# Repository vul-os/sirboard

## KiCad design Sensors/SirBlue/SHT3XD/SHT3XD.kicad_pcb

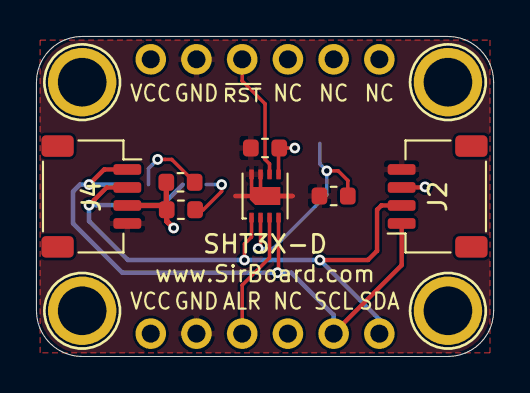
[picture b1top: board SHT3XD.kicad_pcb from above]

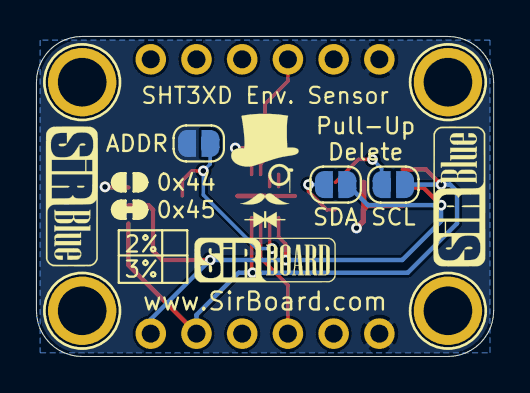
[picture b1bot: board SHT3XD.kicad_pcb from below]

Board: 2 copper layers, 25.4 x 17.8 mm, 16 parts (5 on the bottom side), 9 nets.

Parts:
ADDR: SolderJumper_2_Open; SolderJumper-2_P1.3mm_Open_RoundedPad1.0x1.5mm
C1: C; C_0603_1608Metric
H1, H2, H3, H4: MountingHole; MountingHole_M2.5_SirBoard
J1, J3: Conn_01x06; PinHeader_1x06_P2.54mm_Vertical
J2, J4: Conn_01x04; JST_SH_SM04B-SRSS-TB_1x04-1MP_P1.00mm_Horizontal
R1, R2, R3: 10K; R_0603_1608Metric
SCL: SolderJumper_2_Open; SolderJumper-2_P1.3mm_Open_RoundedPad1.0x1.5mm
SDA: SolderJumper_2_Open; SolderJumper-2_P1.3mm_Open_RoundedPad1.0x1.5mm
U1: SHT3X; DFN2.5X2.5_P=0.5m

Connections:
#RST: J3.3, U1.6
ALERT: J1.3, U1.3
GND: C1.2, J1.2, J2.4, J3.2, J4.4, R3.2, U1.7, U1.8, U1.9
unnamed: ADDR.1, R3.1, U1.2
unnamed: R1.2, SDA.2
unnamed: R2.2, SCL.2
SCL: J1.5, J2.1, J4.1, SCL.1, U1.4
SDA: J1.6, J2.2, J4.2, SDA.1, U1.1
VCC: ADDR.2, C1.1, J1.1, J2.3, J3.1, J4.3, R1.1, R2.1, U1.5

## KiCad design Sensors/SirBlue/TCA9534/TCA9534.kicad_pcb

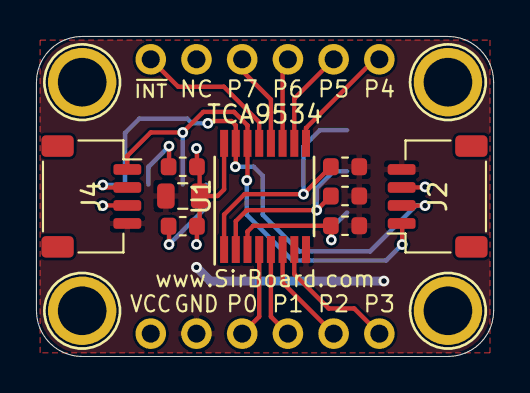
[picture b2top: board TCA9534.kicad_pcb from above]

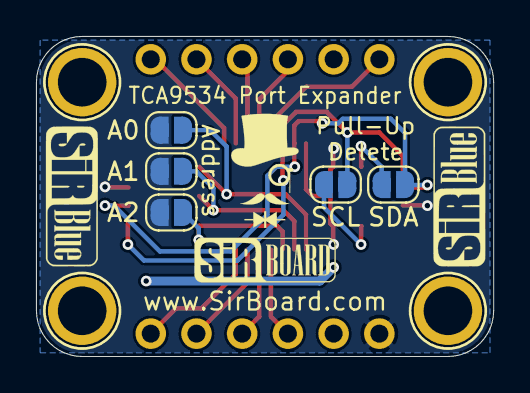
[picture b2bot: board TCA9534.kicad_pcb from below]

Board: 2 copper layers, 25.4 x 17.8 mm, 20 parts (7 on the bottom side), 18 nets.

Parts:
A0, A1, A2: SolderJumper_2_Open; SolderJumper-2_P1.3mm_Open_RoundedPad1.0x1.5mm
C1: 10uF; C_0805_2012Metric
H1, H2, H3, H4: MountingHole; MountingHole_M2.5_SirBoard
J1, J3: Conn_01x06; PinHeader_1x06_P2.54mm_Vertical
J2, J4: Conn_01x04; JST_SH_SM04B-SRSS-TB_1x04-1MP_P1.00mm_Horizontal
R1, R2, R3, R4, R5: 10K; R_0603_1608Metric
SCL: SolderJumper_2_Open; SolderJumper-2_P1.3mm_Open_RoundedPad1.0x1.5mm
SDA: SolderJumper_2_Open; SolderJumper-2_P1.3mm_Open_RoundedPad1.0x1.5mm
U1: TCA9534; TSSOP-16_4.4x5mm_P0.65mm

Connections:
#INT: J3.1, U1.13
/A0: A0.1, R5.1, U1.1
/A1: A1.1, R4.1, U1.2
/A2: A2.1, R3.1, U1.3
GND: C1.2, J1.2, J2.4, J4.4, R3.2, R4.2, R5.2, U1.8
unnamed: R1.2, SCL.2
unnamed: R2.2, SDA.2
P0: J1.3, U1.4
P1: J1.4, U1.5
P2: J1.5, U1.6
P3: J1.6, U1.7
P4: J3.6, U1.9
P5: J3.5, U1.10
P6: J3.4, U1.11
P7: J3.3, U1.12
SCL: J2.1, J4.1, SCL.1, U1.14
SDA: J2.2, J4.2, SDA.1, U1.15
VCC: A0.2, A1.2, A2.2, C1.1, J1.1, J2.3, J4.3, R1.1, R2.1, U1.16

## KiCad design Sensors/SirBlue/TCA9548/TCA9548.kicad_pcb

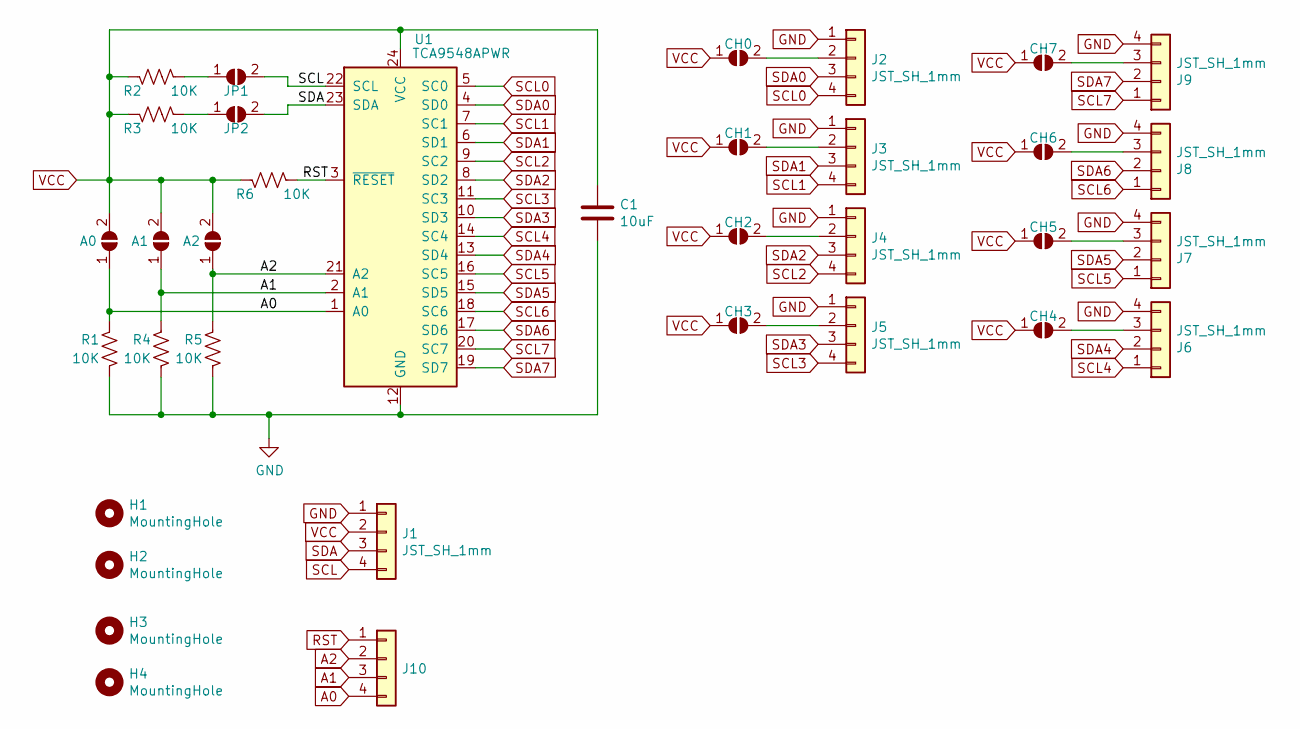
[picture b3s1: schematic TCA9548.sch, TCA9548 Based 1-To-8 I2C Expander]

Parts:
A0, A1, A2: SolderJumper_2_Open; SolderJumper-2_P1.3mm_Open_RoundedPad1.0x1.5mm
C1: 10uF; C_0805_2012Metric; Part C95841
CH0, CH1, CH2, CH3, CH4, CH5, CH6, CH7: SolderJumper_2_Open; SolderJumper-2_P1.3mm_Open_RoundedPad1.0x1.5mm
H1, H2, H3, H4: MountingHole; MountingHole_M2.5_SirBoard
J1, J2, J3, J4, J5, J6, J7, J8, J9: JST_SH_1mm; SirBlue_Connector; Part C160404
J10: 2.54mm; PinHeader_1x04_P2.54mm_Vertical; Part C160404
JP1, JP2: SolderJumper_2_Open; SolderJumper-2_P1.3mm_Open_RoundedPad1.0x1.5mm
R1, R2, R3, R4, R5, R6: 10K; R_0603_1608Metric; Part C99198
U1: TCA9548APWR; TSSOP-24_4.4x7.8mm_P0.65mm; Part C130026

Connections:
A0: A0.1 (A), J10.4, R1.1, U1.1 (A0); also elsewhere on the board
A1: A1.1 (A), J10.3, R4.1, U1.2 (A1); also elsewhere on the board
A2: A2.1 (A), J10.2, R5.1, U1.21 (A2); also elsewhere on the board
GND: C1.2, J1.1, J2.1, J3.1, J4.1, J5.1, J6.4, J7.4, J8.4, J9.4, R1.2, R4.2, R5.2, U1.12 (GND); also elsewhere on the board
unnamed: CH0.2 (B), J2.2
unnamed: CH1.2 (B), J3.2
unnamed: CH2.2 (B), J4.2
unnamed: CH3.2 (B), J5.2
unnamed: CH4.2 (B), J6.3
unnamed: CH5.2 (B), J7.3
unnamed: CH6.2 (B), J8.3
unnamed: CH7.2 (B), J9.3
unnamed 12: JP1.1 (A), R2.2; also elsewhere on the board
unnamed: JP1.2 (B), U1.22 (SCL)
unnamed 14: JP2.1 (A), R3.2; also elsewhere on the board
unnamed: JP2.2 (B), U1.23 (SDA)
RST: J10.1, R6.2, U1.3 (~RESET); also elsewhere on the board
SCL: J1.4; also elsewhere on the board
SCL0: J2.4, U1.5 (SC0); also elsewhere on the board
SCL1: J3.4, U1.7 (SC1); also elsewhere on the board
SCL2: J4.4, U1.9 (SC2); also elsewhere on the board
SCL3: J5.4, U1.11 (SC3); also elsewhere on the board
SCL4: J6.1, U1.14 (SC4); also elsewhere on the board
SCL5: J7.1, U1.16 (SC5); also elsewhere on the board
SCL6: J8.1, U1.18 (SC6); also elsewhere on the board
SCL7: J9.1, U1.20 (SC7); also elsewhere on the board
SDA: J1.3; also elsewhere on the board
SDA0: J2.3, U1.4 (SD0); also elsewhere on the board
SDA1: J3.3, U1.6 (SD1); also elsewhere on the board
SDA2: J4.3, U1.8 (SD2); also elsewhere on the board
SDA3: J5.3, U1.10 (SD3); also elsewhere on the board
SDA4: J6.2, U1.13 (SD4); also elsewhere on the board
SDA5: J7.2, U1.15 (SD5); also elsewhere on the board
SDA6: J8.2, U1.17 (SD6); also elsewhere on the board
SDA7: J9.2, U1.19 (SD7); also elsewhere on the board
VCC: A0.2 (B), A1.2 (B), A2.2 (B), C1.1, CH0.1 (A), CH1.1 (A), CH2.1 (A), CH3.1 (A), CH4.1 (A), CH5.1 (A), CH6.1 (A), CH7.1 (A), J1.2, R2.1, R3.1, R6.1, U1.24 (VCC); also elsewhere on the board

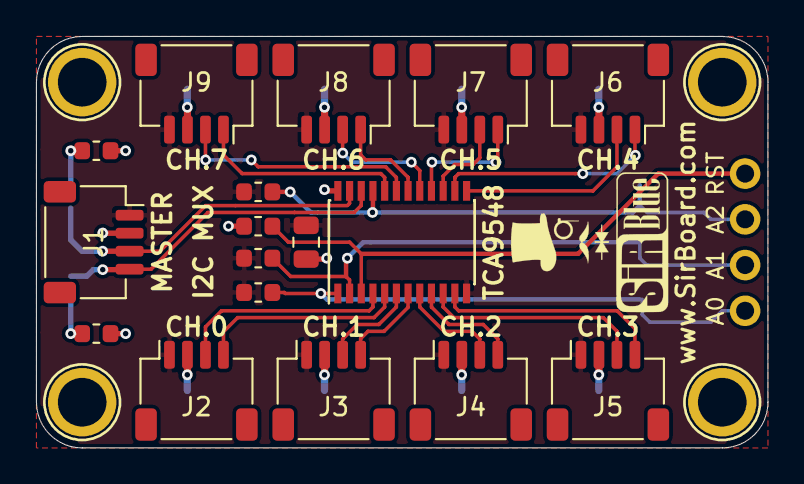
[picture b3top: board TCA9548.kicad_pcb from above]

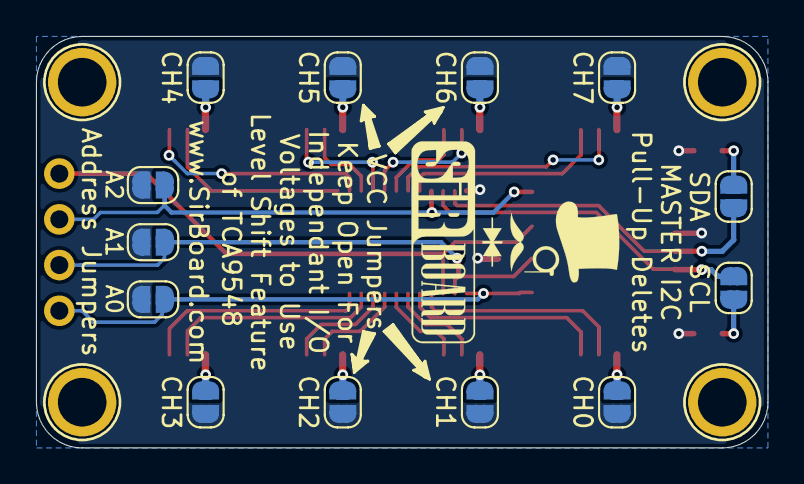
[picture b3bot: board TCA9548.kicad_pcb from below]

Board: 2 copper layers, 40.6 x 22.9 mm, 35 parts (13 on the bottom side), 34 nets.

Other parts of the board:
SCL: SolderJumper_2_Open; SolderJumper-2_P1.3mm_Open_RoundedPad1.0x1.5mm
SDA: SolderJumper_2_Open; SolderJumper-2_P1.3mm_Open_RoundedPad1.0x1.5mm
TCA9548: TCA9548APWR; TSSOP-24_4.4x7.8mm_P0.65mm

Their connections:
A0: TCA9548.1; also elsewhere on the board
A1: TCA9548.2; also elsewhere on the board
A2: TCA9548.21; also elsewhere on the board
GND: TCA9548.12; also elsewhere on the board
unnamed 12: SCL.1; also elsewhere on the board
unnamed 14: SDA.1; also elsewhere on the board
RST: TCA9548.3; also elsewhere on the board
SCL: SCL.2, TCA9548.22; also elsewhere on the board
SCL0: TCA9548.5; also elsewhere on the board
SCL1: TCA9548.7; also elsewhere on the board
SCL2: TCA9548.9; also elsewhere on the board
SCL3: TCA9548.11; also elsewhere on the board
SCL4: TCA9548.14; also elsewhere on the board
SCL5: TCA9548.16; also elsewhere on the board
SCL6: TCA9548.18; also elsewhere on the board
SCL7: TCA9548.20; also elsewhere on the board
SDA: SDA.2, TCA9548.23; also elsewhere on the board
SDA0: TCA9548.4; also elsewhere on the board
SDA1: TCA9548.6; also elsewhere on the board
SDA2: TCA9548.8; also elsewhere on the board
SDA3: TCA9548.10; also elsewhere on the board
SDA4: TCA9548.13; also elsewhere on the board
SDA5: TCA9548.15; also elsewhere on the board
SDA6: TCA9548.17; also elsewhere on the board
SDA7: TCA9548.19; also elsewhere on the board
VCC: TCA9548.24; also elsewhere on the board

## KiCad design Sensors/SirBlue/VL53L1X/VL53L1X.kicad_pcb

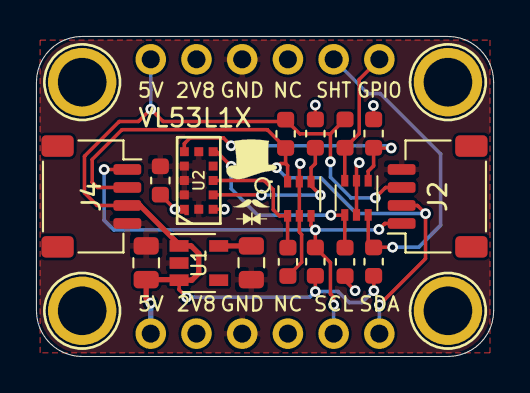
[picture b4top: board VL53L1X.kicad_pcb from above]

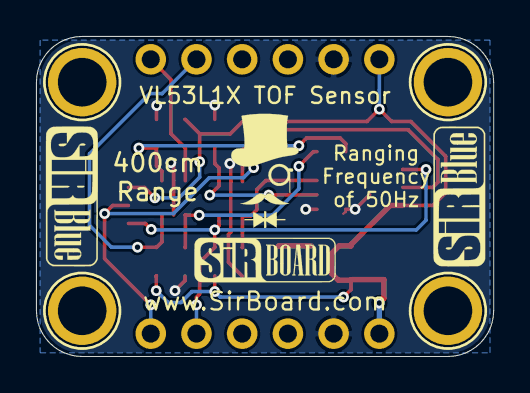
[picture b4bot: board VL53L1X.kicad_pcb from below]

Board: 2 copper layers, 25.4 x 17.8 mm, 23 parts (2 on the bottom side), 12 nets.

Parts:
C1, C4: 10uF; C_0805_2012Metric
C2: 100nF; C_0603_1608Metric
H1, H2, H3, H4: MountingHole; MountingHole_M2.5_SirBoard
J1, J3: Conn_01x06; PinHeader_1x06_P2.54mm_Vertical
J2, J4: Conn_01x04; JST_SH_SM04B-SRSS-TB_1x04-1MP_P1.00mm_Horizontal
Q1, Q2: BSS138DW; SOT-363_SC-70-6
R1, R2, R3, R4, R5, R6, R7, R8: 10K; R_0603_1608Metric
U1: AP2127K-2.8; SOT-23-5
U2: VL53L1; LGA-12-2.4X4.8

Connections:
2V8: C2.1, J1.2, J3.2, Q1.2, Q1.5, Q2.2, Q2.5, R1.2, R3.2, R5.2, R7.2, U2.1, U2.11
5V: C1.1, J1.1, J2.3, J3.1, J4.3, R2.1, R4.1, R6.1, R8.1, U1.1, U1.3
GND: C1.2, C2.2, C4.2, J1.3, J2.4, J3.3, J4.4, U1.2, U2.2, U2.3, U2.4, U2.6, U2.12
GPIO_2V8: Q1.4, R3.1, U2.7
GPIO_5V: J3.6, Q1.3, R4.2
unnamed: C4.1, U1.5
SCL_2V8: Q2.1, R5.1, U2.10
SCL_5V: J1.5, J2.1, J4.1, Q2.6, R6.2
SDA_2V8: Q2.4, R7.1, U2.9
SDA_5V: J1.6, J2.2, J4.2, Q2.3, R8.2
XSHUT_2V8: Q1.1, R1.1, U2.5
XSHUT_5V: J3.5, Q1.6, R2.2
